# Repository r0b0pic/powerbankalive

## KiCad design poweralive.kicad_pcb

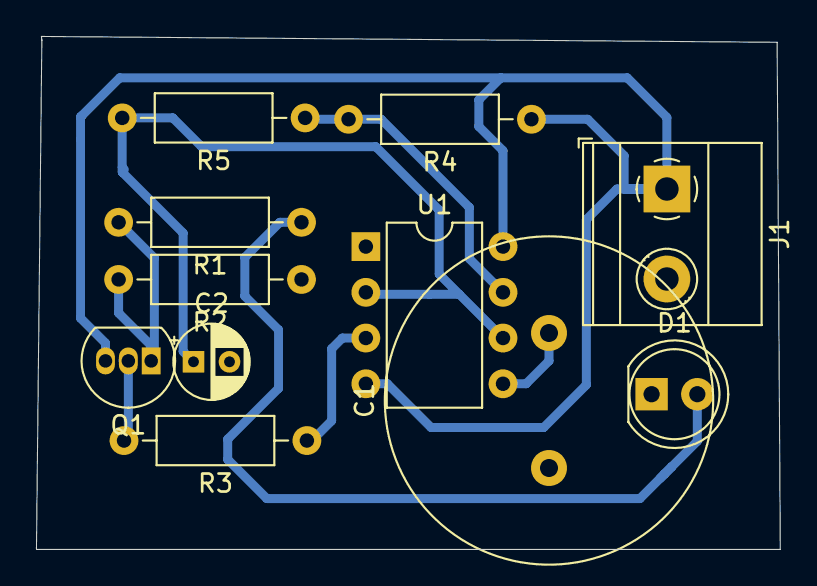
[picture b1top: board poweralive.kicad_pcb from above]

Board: 2 copper layers, 41.3 x 28.5 mm, 11 parts (0 on the bottom side), 7 nets.

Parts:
C1: 0.1 uF; C_Radial_D18.0mm_H35.5mm_P7.50mm
C2: 47 uF; CP_Radial_D4.0mm_P2.00mm
D1: LED; LED_D5.0mm
J1: Screw_Terminal_01x02; TerminalBlock_Phoenix_MKDS-1,5-2_1x02_P5.00mm_Horizontal
Q1: BC327; TO-92_Inline
R1: 390; R_Axial_DIN0207_L6.3mm_D2.5mm_P10.16mm_Horizontal
R2: 22; R_Axial_DIN0207_L6.3mm_D2.5mm_P10.16mm_Horizontal
R3: 1K; R_Axial_DIN0207_L6.3mm_D2.5mm_P10.16mm_Horizontal
R4: 220K; R_Axial_DIN0207_L6.3mm_D2.5mm_P10.16mm_Horizontal
R5: 33K; R_Axial_DIN0207_L6.3mm_D2.5mm_P10.16mm_Horizontal
U1: NE555P; DIP-8_W7.62mm

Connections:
+5V: C1.2, C2.1, J1.1, Q1.3, R4.1, R5.2, U1.2, U1.4, U1.5, U1.6, U1.8
GND: C1.1, C2.2, D1.1, J1.2, R2.1, U1.1
unnamed: D1.2, R1.1
unnamed: Q1.1, R1.2, R2.2
unnamed: Q1.2, R3.2
unnamed: R3.1, U1.3
unnamed: R4.2, R5.1, U1.7

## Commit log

2023-04-29 ajout des fichiers au dépôt
